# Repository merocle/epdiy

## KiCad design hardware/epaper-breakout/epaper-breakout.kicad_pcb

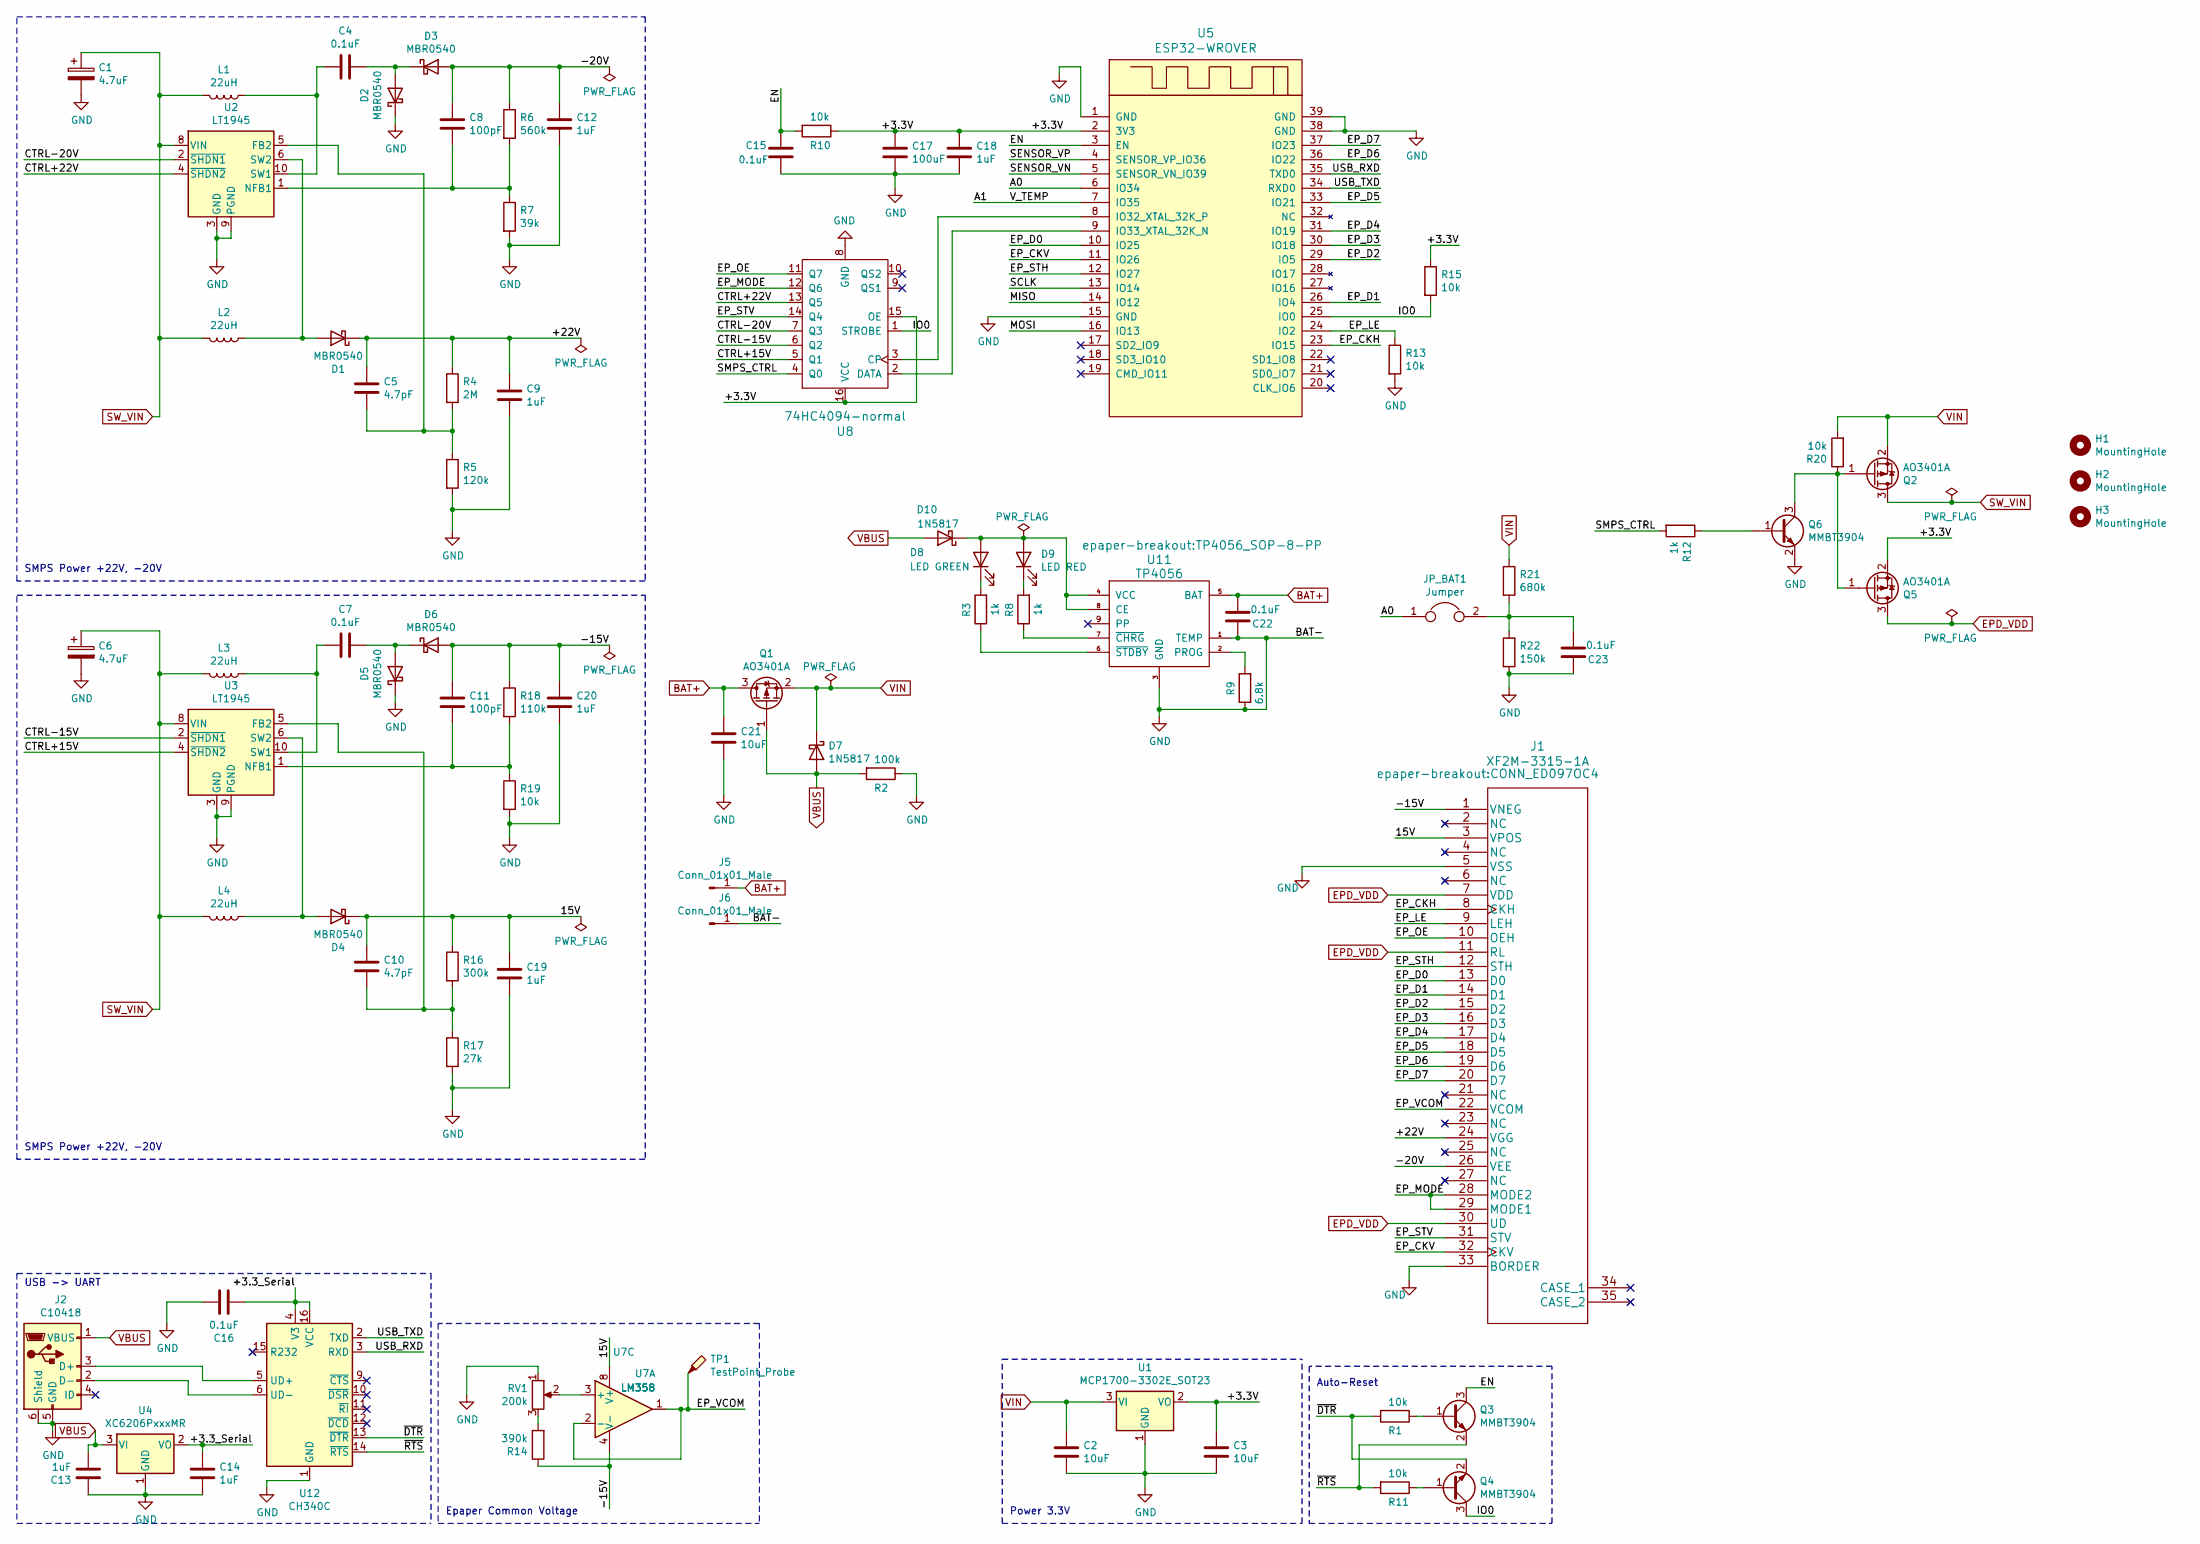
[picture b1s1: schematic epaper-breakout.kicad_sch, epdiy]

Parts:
C1, C6: 4.7uF; C_0603_1608Metric; LCSC C19666
C2, C3, C21: 10uF; C_0603_1608Metric; LCSC C19702
C4, C7, C16, C22, C23: 0.1uF; C_0603_1608Metric; LCSC C14663
C5, C10: 4.7pF; C_0603_1608Metric; LCSC C1669
C8, C11: 100pF; C_0603_1608Metric; LCSC C14858
C9, C12, C13, C14, C18, C19, C20: 1uF; C_0603_1608Metric; LCSC C15849
C15: 0.1uF; C_0603_1608Metric; LCSC C1588
C17: 100uF; CP_EIA-3528-15_AVX-H; LCSC C16133
D1, D2, D3, D4, D5, D6: MBR0540; D_SOD-123; LCSC C21353
D7, D10: 1N5817; D_SOD-123; LCSC C8598
D8: LED GREEN; LED_0805_2012Metric; LCSC C2297
D9: LED RED; LED_0805_2012Metric; LCSC C84256
H1, H2, H3: MountingHole; MountingHole_2.2mm_M2
J1: XF2M-3315-1A; CONN_ED097OC4; LCSC C231420
J2: C10418; USB_Micro-B_A01SB141B1-067; LCSC C10418
J5, J6: Conn_01x01_Male; PinHeader_1x01_P2.54mm_Vertical
JP_BAT1: Jumper; SolderJumper-2_P1.3mm_Bridged2Bar_RoundedPad1.0x1.5mm
L1, L2, L3, L4: 22uH; L_6.3x6.3_H3; LCSC C206321
Q1, Q2, Q5: AO3401A; SOT-23; LCSC C15127
Q3, Q4, Q6: MMBT3904; SOT-23; LCSC C20526
R1, R10, R11, R13, R15, R19, R20: 10k; R_0805_2012Metric; LCSC C17414
R2: 100k; R_0805_2012Metric; LCSC C17407
R3, R8, R12: 1k; R_0805_2012Metric; LCSC C17513
R4: 2M; R_0805_2012Metric; LCSC C26112
R5: 120k; R_0805_2012Metric; LCSC C17436
R6: 560k; R_0805_2012Metric; LCSC C15785
R7: 39k; R_0805_2012Metric; LCSC C25826
R9: 6.8k; R_0805_2012Metric; LCSC C17772
R14: 390k; R_0805_2012Metric; LCSC C17656
R16: 300k; R_0805_2012Metric; LCSC C17616
R17: 27k; R_0805_2012Metric; LCSC C17593
R18: 110k; R_0805_2012Metric; LCSC C17422
R21: 680k; R_0805_2012Metric; LCSC C17797
R22: 150k; R_0805_2012Metric; LCSC C17470
RV1: 200k; EVM3ESX50B25; LCSC C11958
TP1: TestPoint_Probe; TestPoint_Pad_D1.0mm
U1: MCP1700-3302E_SOT23; SOT-23; LCSC C39051
U2, U3: LT1945; MSOP-10_3x3mm_P0.5mm
U4: XC6206PxxxMR; SOT-23; LCSC C5446
U5: ESP32-WROVER; LCSC C503591
U7: LM358; SOP-8_3.76x4.96mm_P1.27mm; LCSC C7950
U8: 74HC4094-normal; SOIC-16_3.9x9.9mm_P1.27mm; LCSC C5651
U11: TP4056; TP4056_SOP-8-PP; LCSC C16581
U12: CH340C; SOIC-16_3.9x9.9mm_P1.27mm; LCSC C84681

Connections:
/15V: C10.2, C19.2, D4.1 (K), J1.3 (VPOS), R16.1, U7.8 (V+)
/+3.3V: C3.2, C17.1, C18.2, Q5.2 (S), R10.1, R15.1, U1.2 (VO), U5.2 (3V3), U8.15 (OE), U8.16 (VCC)
/+3.3_Serial: C14.2, C16.1, U4.2 (VO), U12.4 (V3), U12.16 (VCC)
/+22V: C5.2, C9.2, D1.1 (K), J1.24 (VGG), R4.1
/-15V: C11.2, C20.2, D6.2 (A), J1.1 (VNEG), R14.1, R18.1, U7.4 (V-)
/-20V: C8.2, C12.2, D3.2 (A), J1.26 (VEE), R6.1
/A0: JP_BAT1.1, U5.6 (IO34)
/A1: U5.7 (IO35)
/CTRL+15V: U3.4 (~SHDN2), U8.5 (Q1)
/CTRL+22V: U2.4 (~SHDN2), U8.13 (Q5)
/CTRL-15V: U3.2 (~SHDN1), U8.6 (Q2)
/CTRL-20V: U2.2 (~SHDN1), U8.7 (Q3)
/EN: C15.1, Q3.3 (C), R10.2, U5.3 (EN)
/EP_CKH: J1.8 (CKH), U5.23 (IO15)
/EP_CKV: J1.32 (CKV), U5.11 (IO26)
/EP_D0: J1.13 (D0), U5.10 (IO25)
/EP_D1: J1.14 (D1), U5.26 (IO4)
/EP_D2: J1.15 (D2), U5.29 (IO5)
/EP_D3: J1.16 (D3), U5.30 (IO18)
/EP_D4: J1.17 (D4), U5.31 (IO19)
/EP_D5: J1.18 (D5), U5.33 (IO21)
/EP_D6: J1.19 (D6), U5.36 (IO22)
/EP_D7: J1.20 (D7), U5.37 (IO23)
/EP_LE: J1.9 (LEH), R13.1, U5.24 (IO2)
/EP_MODE: J1.28 (MODE2), J1.29 (MODE1), U8.12 (Q6)
/EP_OE: J1.10 (OEH), U8.11 (Q7)
/EP_STH: J1.12 (STH), U5.12 (IO27)
/EP_STV: J1.31 (STV), U8.14 (Q4)
/EP_VCOM: J1.22 (VCOM), TP1.1, U7.1, U7.2 (-)
/IO0: Q4.3 (C), R15.2, U5.25 (IO0), U8.1 (STROBE)
/MISO: U5.14 (IO12)
/MOSI: U5.16 (IO13)
/SCLK: U5.13 (IO14)
/SENSOR_VN: U5.5 (SENSOR_VN_IO39)
/SENSOR_VP: U5.4 (SENSOR_VP_IO36)
/SMPS_CTRL: R12.2, U8.4 (Q0)
/USB_RXD: U5.35 (TXD0), U12.3 (RXD)
/USB_TXD: U5.34 (RXD0), U12.2 (TXD)
/~DTR: Q4.2 (E), R1.2, U12.13 (~DTR)
/~RTS: Q3.2 (E), R11.2, U12.14 (~RTS)
BAT+: C21.1, C22.2, J5.1, Q1.3 (D), U11.5 (BAT)
EPD_VDD: J1.7 (VDD), J1.11 (RL), J1.30 (UD), Q5.3 (D)
GND: C1.2, C2.1, C3.1, C6.2, C9.1, C12.1, C13.2, C14.1, C15.2, C16.2, C17.2, C18.1, C19.1, C20.1, C21.2, C22.1, C23.1, D2.1 (K), D5.1 (K), J1.5 (VSS), J1.33 (BORDER), J2.5 (GND), J2.6 (Shield), J6.1, Q6.2 (E), R2.1, R5.2, R7.2, R9.1, R13.2, R17.2, R19.2, R22.2, RV1.1, U1.1 (GND), U2.3 (GND), U2.7 (PGND), U2.9 (PGND), U3.3 (GND), U3.7 (PGND), U3.9 (PGND), U4.1 (GND), U5.1 (GND), U5.15 (GND), U5.38 (GND), U5.39 (GND), U8.8 (GND), U11.1 (TEMP), U11.3 (GND), U12.1 (GND)
unnamed: C4.1, D2.2 (A), D3.1 (K)
unnamed: C4.2, L1.1, U2.10 (SW1)
unnamed: C5.1, R4.2, R5.1, U2.5 (FB2)
unnamed: C7.1, D5.2 (A), D6.1 (K)
unnamed: C7.2, L3.1, U3.10 (SW1)
unnamed: C8.1, R6.2, R7.1, U2.1 (NFB1)
unnamed: C10.1, R16.2, R17.1, U3.5 (FB2)
unnamed: C11.1, R18.2, R19.1, U3.1 (NFB1)
unnamed: C23.2, JP_BAT1.2, R21.2, R22.1
unnamed: D1.2 (A), L2.1, U2.6 (SW2)
unnamed: D4.2 (A), L4.1, U3.6 (SW2)
unnamed: D8.1 (K), R3.2
unnamed: D9.1 (K), R8.2
unnamed: D8.2 (A), D9.2 (A), D10.1 (K), U11.4 (VCC), U11.8 (CE)
unnamed: J2.2 (D-), U12.6 (UD-)
unnamed: J2.3 (D+), U12.5 (UD+)
unnamed: Q2.1 (G), Q5.1 (G), Q6.3 (C), R20.1
unnamed: Q3.1 (B), R1.1
unnamed: Q4.1 (B), R11.1
unnamed: Q6.1 (B), R12.1
unnamed: R3.1, U11.6 (~STDBY)
unnamed: R8.1, U11.7 (~CHRG)
unnamed: R9.2, U11.2 (PROG)
unnamed: R14.2, RV1.3
unnamed: RV1.2, U7.3 (+)
unnamed: U5.8 (IO32_XTAL_32K_P), U8.3 (CP)
unnamed: U5.9 (IO33_XTAL_32K_N), U8.2 (DATA)
SW_VIN: C1.1, C6.1, L1.2, L2.2, L3.2, L4.2, Q2.3 (D), U2.8 (VIN), U3.8 (VIN)
VBUS: C13.1, D7.2 (A), D10.2 (A), J2.1 (VBUS), Q1.1 (G), R2.2, U4.3 (VI)
VIN: C2.2, D7.1 (K), Q1.2 (S), Q2.2 (S), R20.2, R21.1, U1.3 (VI)

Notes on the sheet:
SMPS Power +22V, -20V
USB -> UART
Epaper Common Voltage
Power 3.3V
Auto-Reset

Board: 2 copper layers, 80 parts (0 on the bottom side), 66 nets, no tracks yet.

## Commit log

2021-07-08 saved in new format

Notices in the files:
hardware/epaper-breakout/epaper-breakout.kicad_sch:
License: CC-BY-SA-4.0
parts and their libraries:
Copyright 2016 Accelerated Designs. All rights reserved.
